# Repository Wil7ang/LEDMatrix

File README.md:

LEDMatrix
=========

LED Matrix display firmware.

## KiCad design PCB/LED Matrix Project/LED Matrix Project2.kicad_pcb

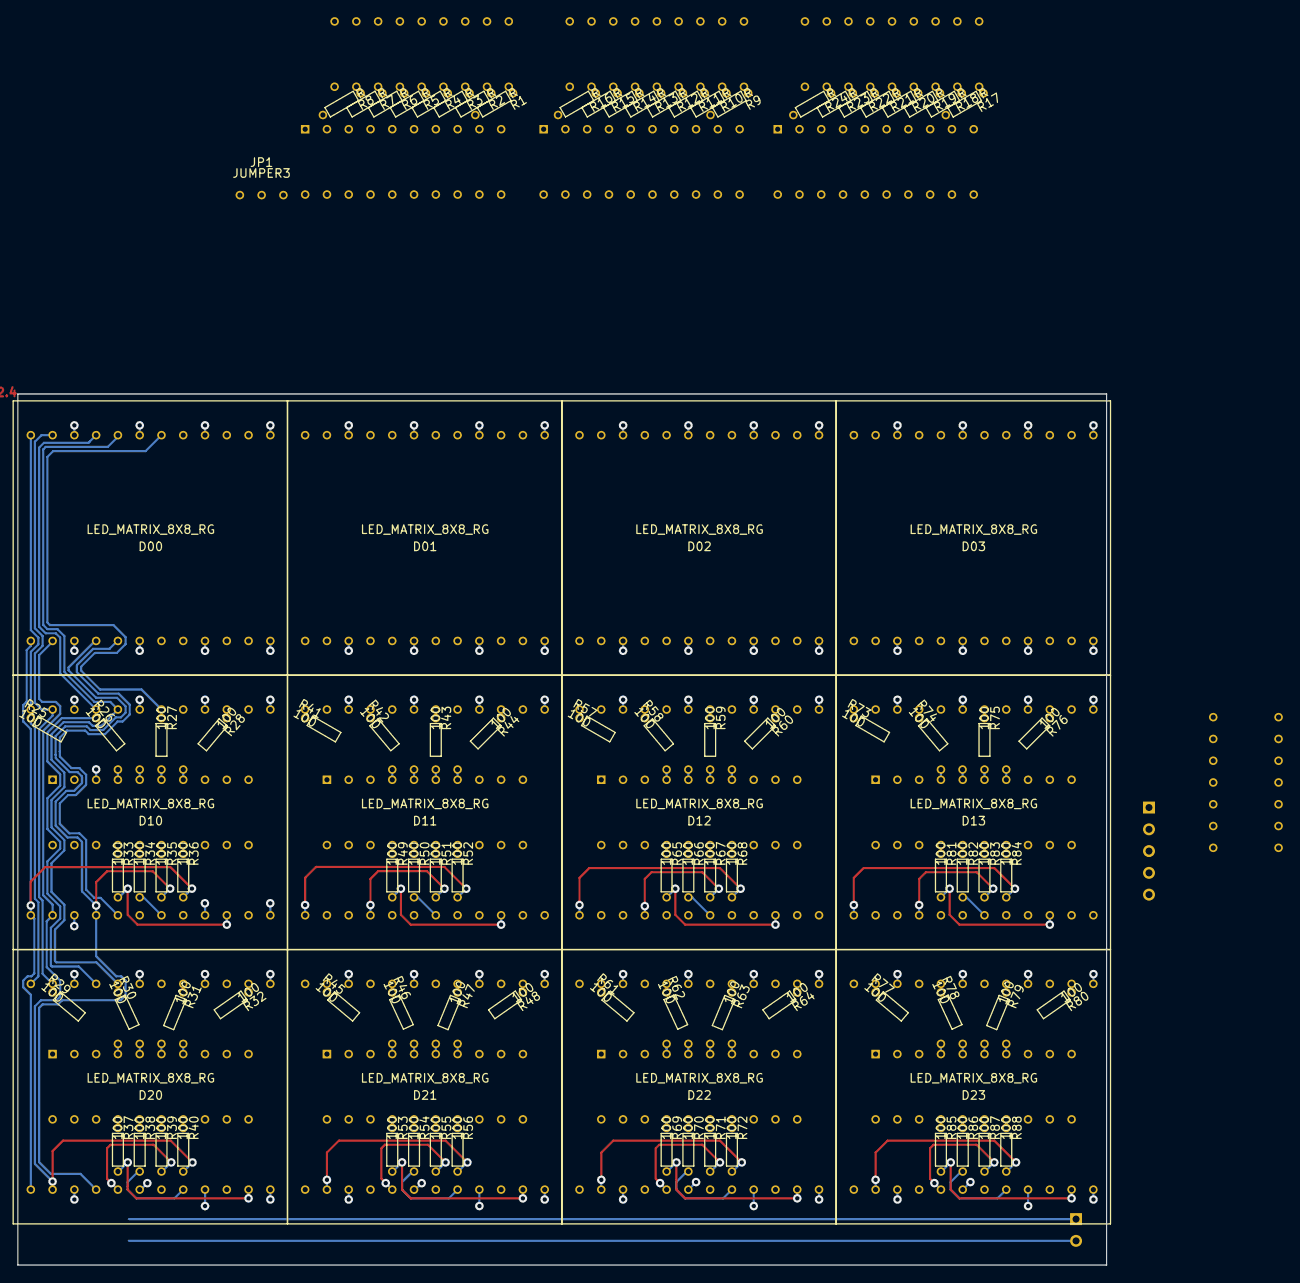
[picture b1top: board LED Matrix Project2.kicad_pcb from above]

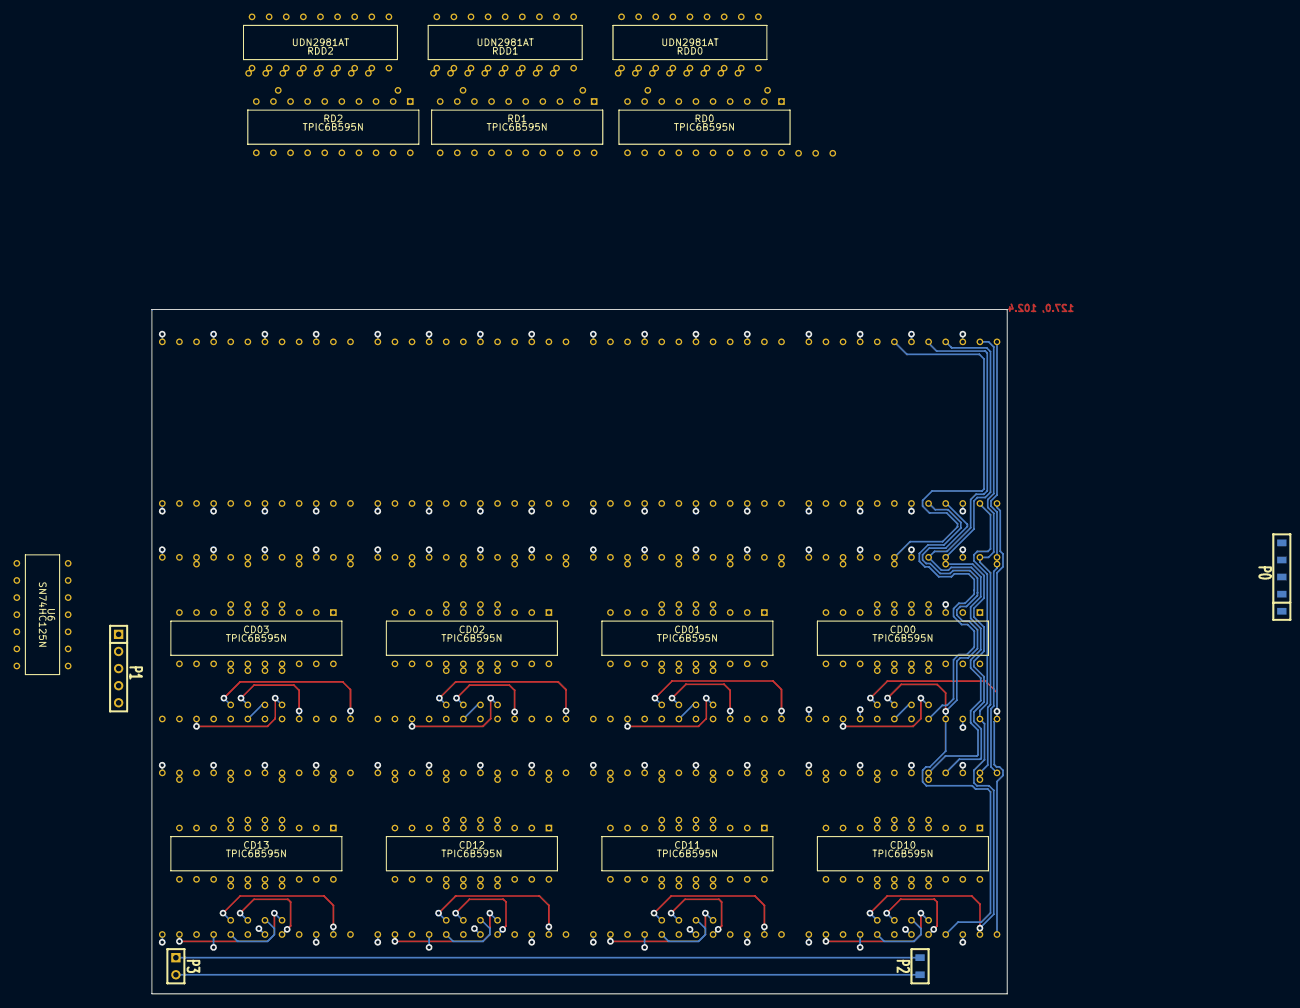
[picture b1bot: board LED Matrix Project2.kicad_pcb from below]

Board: 2 copper layers, 127.0 x 101.6 mm, 120 parts (19 on the bottom side), 199 nets.

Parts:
CD00, CD01, CD02, CD03, CD10, CD11, CD12, CD13: TPIC6B595N; TPIC6B595N-DIP
D00, D01, D02, D03, D10, D11, D12, D13, D20, D21, D22, D23: LED_MATRIX_8X8_RG; LEDMatrix8x8
JP1: JUMPER3; 3-Jumper
P0, P1: CONN_5; SIL-5
P2, P3: CONN_2; SIL-2
R1, R2, R3, R4, R5, R6, R7, R8, R9, R10, R11, R12, R13, R14, R15, R16, R17, R18, R19, R20, R21, R22, R23, R24: R; 1-8Resistor
R25, R26, R27, R28, R29, R30, R31, R32, R33, R34, R35, R36, R37, R38, R39, R40, R41, R42, R43, R44, R45, R46, R47, R48, R49, R50, R51, R52, R53, R54, R55, R56, R57, R58, R59, R60, R61, R62, R63, R64, R65, R66, R67, R68, R69, R70, R71, R72, R73, R74, R75, R76, R77, R78, R79, R80, R81, R82, R83, R84, R85, R86, R87, R88: 100; 1-8Resistor
RD0, RD1, RD2: TPIC6B595N; TPIC6B595N-DIP
RDD0, RDD1, RDD2: UDN2981AT
U6: SN74HC125N

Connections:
5Vcc: CD00.2, CD00.8, CD01.2, CD01.8, CD02.2, CD02.8, CD03.2, CD03.8, CD10.2, CD10.8, CD11.2, CD11.8, CD12.2, CD12.8, CD13.2, CD13.8, P2.2, P3.1, R1.2, R8.2, R9.2, R16.2, R17.2, R24.2, RD0.2, RD0.8, RD1.2, RD1.8, RD2.2, RD2.8, RDD0.9, RDD1.9, RDD2.9, U6.14
DATA IN: P0.3, RD0.3, U6.9
DATA IN 2: JP1.1, P0.1
DATA OUT: P1.5, U6.11
DATA OUT 1: P1.3, U6.8
DATA OUT RED: CD03.18, CD10.3
G: CD00.9, CD01.9, CD02.9, CD03.9, CD10.9, CD11.9, CD12.9, CD13.9, P0.2, P1.4, RD0.9, RD1.9, RD2.9
GND: CD00.10, CD00.11, CD00.19, CD01.10, CD01.11, CD01.19, CD02.10, CD02.11, CD02.19, CD03.10, CD03.11, CD03.19, CD10.10, CD10.11, CD10.19, CD11.10, CD11.11, CD11.19, CD12.10, CD12.11, CD12.19, CD13.10, CD13.11, CD13.19, P2.1, P3.2, RD0.10, RD0.11, RD0.19, RD1.10, RD1.11, RD1.19, RD2.10, RD2.11, RD2.19, RDD0.10, RDD1.10, RDD2.10, U6.1, U6.4, U6.7, U6.10, U6.13
unnamed: D03.4, D13.4, D23.4, R83.2
unnamed: D03.1, D13.1, D23.1, R84.2
unnamed: D03.7, D13.7, D23.7, R82.2
unnamed: D03.10, D13.10, D23.10, R81.2
unnamed: D10.3, D11.3, D12.3, D13.3, RDD1.15
unnamed: R23.1, RD2.6, RDD2.7
unnamed: R24.1, RD2.7, RDD2.8
unnamed: R22.1, RD2.5, RDD2.6
unnamed: R21.1, RD2.4, RDD2.5
unnamed: R17.1, RD2.17, RDD2.1
unnamed: R20.1, RD2.14, RDD2.4
unnamed: R19.1, RD2.15, RDD2.3
unnamed: R18.1, RD2.16, RDD2.2
unnamed: D00.21, D10.21, D20.21, R26.1
unnamed: D03.15, D13.15, D23.15, R76.1
unnamed: D03.18, D13.18, D23.18, R75.1
unnamed: D03.21, D13.21, D23.21, R74.1
unnamed: D03.24, D13.24, D23.24, R73.1
unnamed: D03.8, D13.8, D23.8, R86.2
unnamed: D03.2, D13.2, D23.2, R88.2
unnamed: D03.14, D13.14, D23.14, R80.1
unnamed: D03.17, D13.17, D23.17, R79.1
unnamed: D03.20, D13.20, D23.20, R78.1
unnamed: D03.23, D13.23, D23.23, R77.1
unnamed: D01.24, D11.24, D21.24, R41.1
unnamed: D10.12, D11.12, D12.12, D13.12, RDD1.18
unnamed: D10.9, D11.9, D12.9, D13.9, RDD1.17
unnamed: D10.6, D11.6, D12.6, D13.6, RDD1.16
unnamed: R13.1, RD1.4, RDD1.5
unnamed: R10.1, RD1.16, RDD1.2
unnamed: R9.1, RD1.17, RDD1.1
unnamed: R14.1, RD1.5, RDD1.6
unnamed: R11.1, RD1.15, RDD1.3
unnamed: R12.1, RD1.14, RDD1.4
unnamed: D10.13, D11.13, D12.13, D13.13, RDD1.11
unnamed: D10.16, D11.16, D12.16, D13.16, RDD1.12
unnamed: D10.19, D11.19, D12.19, D13.19, RDD1.13
unnamed: D10.22, D11.22, D12.22, D13.22, RDD1.14
unnamed: R16.1, RD1.7, RDD1.8
unnamed: R15.1, RD1.6, RDD1.7
unnamed: CD00.18, CD01.3
unnamed: CD01.18, CD02.3
unnamed: CD02.18, CD03.3
unnamed: CD10.18, CD11.3
unnamed: CD11.18, CD12.3
unnamed: CD12.18, CD13.3
unnamed: CD00.3, JP1.2
unnamed: JP1.3, RD2.18
unnamed: RD1.18, RD2.3
unnamed: RD0.18, RD1.3
unnamed: CD13.18, U6.12
unnamed: D20.19, D21.19, D22.19, D23.19, RDD2.13
unnamed: D20.13, D21.13, D22.13, D23.13, RDD2.11
unnamed: D20.3, D21.3, D22.3, D23.3, RDD2.15
unnamed: D20.9, D21.9, D22.9, D23.9, RDD2.17
unnamed: D20.22, D21.22, D22.22, D23.22, RDD2.14
unnamed: D20.16, D21.16, D22.16, D23.16, RDD2.12
unnamed: D20.12, D21.12, D22.12, D23.12, RDD2.18
unnamed: D20.6, D21.6, D22.6, D23.6, RDD2.16
unnamed: D02.21, D12.21, D22.21, R58.1
unnamed: D02.15, D12.15, D22.15, R60.1
unnamed: D02.20, D12.20, D22.20, R62.1
unnamed: D00.20, D10.20, D20.20, R30.1
unnamed: D00.15, D10.15, D20.15, R28.1
unnamed: D03.5, D13.5, D23.5, R87.2
unnamed: D03.11, D13.11, D23.11, R85.2
unnamed: CD12.17, R69.1
unnamed: D02.11, D12.11, D22.11, R69.2
unnamed: D02.14, D12.14, D22.14, R64.1
unnamed: CD12.7, R64.2
unnamed: D02.17, D12.17, D22.17, R63.1
unnamed: CD12.6, R63.2
unnamed: CD12.5, R62.2
unnamed: CD12.4, R61.2
unnamed: CD03.16, R82.1
unnamed: CD03.17, R81.1
unnamed: CD03.14, R84.1
unnamed: CD03.15, R83.1
unnamed: CD03.7, R76.2
unnamed: CD03.6, R75.2
unnamed: CD03.5, R74.2
unnamed: CD03.4, R73.2
unnamed: CD02.14, R68.1
unnamed: CD02.15, R67.1
unnamed: CD02.16, R66.1
unnamed: CD02.17, R65.1
unnamed: D02.1, D12.1, D22.1, R68.2
unnamed: D02.7, D12.7, D22.7, R66.2
unnamed: CD02.7, R60.2
unnamed: CD02.6, R59.2
unnamed: CD02.5, R58.2
unnamed: CD02.4, R57.2
unnamed: CD12.14, R72.1
unnamed: CD12.15, R71.1
unnamed: CD12.16, R70.1
unnamed: D02.2, D12.2, D22.2, R72.2
unnamed: D02.18, D12.18, D22.18, R59.1
unnamed: CD13.14, R88.1
unnamed: CD13.15, R87.1
unnamed: CD13.16, R86.1
unnamed: CD13.17, R85.1
unnamed: CD13.7, R80.2
unnamed: CD13.6, R79.2
unnamed: CD13.5, R78.2
unnamed: CD13.4, R77.2
unnamed: CD10.16, R38.1
unnamed: CD10.17, R37.1
unnamed: D00.11, D10.11, D20.11, R37.2
unnamed: D00.14, D10.14, D20.14, R32.1
unnamed: CD10.7, R32.2
unnamed: D00.17, D10.17, D20.17, R31.1
unnamed: CD10.6, R31.2
unnamed: CD10.5, R30.2
unnamed: CD10.4, R29.2
unnamed: R5.1, RD0.4, RDD0.5
unnamed: CD10.15, R39.1
unnamed: CD10.14, R40.1
unnamed: D00.2, D10.2, D20.2, R40.2
unnamed: R4.1, RD0.14, RDD0.4
unnamed: R6.1, RD0.5, RDD0.6
unnamed: R7.1, RD0.6, RDD0.7
unnamed: R8.1, RD0.7, RDD0.8
unnamed: R1.1, RD0.17, RDD0.1
unnamed: R2.1, RD0.16, RDD0.2
unnamed: D00.24, D10.24, D20.24, R25.1
unnamed: D00.23, D10.23, D20.23, R29.1
unnamed: CD00.4, R25.2
unnamed: CD00.5, R26.2
unnamed: CD00.6, R27.2
unnamed: CD00.7, R28.2
unnamed: D00.10, D10.10, D20.10, R33.2
unnamed: D00.8, D10.8, D20.8, R38.2
unnamed: D00.5, D10.5, D20.5, R39.2
unnamed: D00.4, D10.4, D20.4, R35.2
unnamed: CD00.17, R33.1
unnamed: D00.18, D10.18, D20.18, R27.1
unnamed: D00.7, D10.7, D20.7, R34.2
unnamed: CD00.16, R34.1
unnamed: CD00.15, R35.1
unnamed: D00.1, D10.1, D20.1, R36.2
unnamed: CD00.14, R36.1
unnamed: CD11.14, R56.1
unnamed: CD11.7, R48.2
unnamed: CD11.6, R47.2
unnamed: CD11.15, R55.1
unnamed: CD11.16, R54.1
unnamed: CD11.17, R53.1
unnamed: D01.2, D11.2, D21.2, R56.2
unnamed: CD11.5, R46.2
unnamed: CD11.4, R45.2
unnamed: CD01.4, R41.2
unnamed: CD01.5, R42.2
unnamed: D01.21, D11.21, D21.21, R42.1
unnamed: CD01.6, R43.2
unnamed: D01.18, D11.18, D21.18, R43.1
unnamed: CD01.7, R44.2
unnamed: D01.15, D11.15, D21.15, R44.1
unnamed: CD01.17, R49.1
unnamed: D02.4, D12.4, D22.4, R67.2
unnamed: D02.5, D12.5, D22.5, R71.2
unnamed: D02.8, D12.8, D22.8, R70.2
unnamed: D02.10, D12.10, D22.10, R65.2
unnamed: D02.23, D12.23, D22.23, R61.1
unnamed: D02.24, D12.24, D22.24, R57.1
unnamed: D01.7, D11.7, D21.7, R50.2
unnamed: D01.20, D11.20, D21.20, R46.1
unnamed: D01.17, D11.17, D21.17, R47.1
unnamed: D01.14, D11.14, D21.14, R48.1
unnamed: D01.11, D11.11, D21.11, R53.2
unnamed: D01.8, D11.8, D21.8, R54.2
unnamed: D01.4, D11.4, D21.4, R51.2
unnamed: D01.5, D11.5, D21.5, R55.2
unnamed: D01.10, D11.10, D21.10, R49.2
unnamed: D00.12, D01.12, D02.12, D03.12, RDD0.18
unnamed: D01.23, D11.23, D21.23, R45.1
unnamed: CD01.14, R52.1
unnamed: CD01.15, R51.1
unnamed: CD01.16, R50.1
unnamed: D01.1, D11.1, D21.1, R52.2
unnamed: D00.9, D01.9, D02.9, D03.9, RDD0.17
unnamed: D00.3, D01.3, D02.3, D03.3, RDD0.15
unnamed: D00.6, D01.6, D02.6, D03.6, RDD0.16
unnamed: R3.1, RD0.15, RDD0.3
unnamed: D00.19, D01.19, D02.19, D03.19, RDD0.13
unnamed: D00.22, D01.22, D02.22, D03.22, RDD0.14
unnamed: D00.16, D01.16, D02.16, D03.16, RDD0.12
unnamed: D00.13, D01.13, D02.13, D03.13, RDD0.11
RCK: CD00.12, CD01.12, CD02.12, CD03.12, CD10.12, CD11.12, CD12.12, CD13.12, P0.4, RD0.12, RD1.12, RD2.12, U6.5
RCK OUT: P1.2, U6.6
SRCK: CD00.13, CD01.13, CD02.13, CD03.13, CD10.13, CD11.13, CD12.13, CD13.13, P0.5, RD0.13, RD1.13, RD2.13, U6.2
SRCK OUT: P1.1, U6.3

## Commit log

2014-02-26 Initial code commit
2014-02-26 Add build script
2014-02-26 Fix std typo
2014-02-26 Fix missed semicolon
2014-02-26 Add font argument
2014-02-26 Error const char* should be cool
2014-02-26 Switch to targa font
2014-02-26 Unreverse characters
2014-02-26 Exclude tiny font from big font
2014-02-26 Reduce to 16
2014-02-26 Add initial support for tiny text
2014-02-26 Change position to reference correct tinyposition
2014-02-26 Add clock
2014-02-26 Hard fix for tiny ‘4’
2014-02-26 Catch run away no internet connection condition
2014-02-26 Changed time check location
2014-02-26 pthread fix
2014-02-26 Reorder definitions
2014-02-26 Fix string erase index
2014-02-26 Change time color to green
2014-02-26 Add support for negative offset
2014-02-26 Delay pthread
2014-02-26 Correct thread
2014-02-26 Add second argument to pthread_join
2014-02-27 Attempt fix at no internet crash
2014-02-27 Fix reload
2014-02-27 Add negative start offset
2014-02-27 Temporary disable offset increment
2014-02-27 Changed negative offset
2014-02-27 Add more print
2014-02-27 Test
2014-02-27 Fix start position
2014-02-27 Offset clock
2014-02-27 Increase text speed
2014-02-27 Add join thread
2014-02-28 Added CNN news source
2014-02-28 Fix color change
2014-02-28 Add PCB files
2014-03-02 Free mrss data
2014-03-02 Add engadget feed
2014-03-02 Fix typo
2014-03-02 Increase speed to 6
2014-03-09 Increase size to final 30
2014-03-09 Increase hwdebug time
2014-03-09 Disable hwdebug
2014-03-10 Change SPI speed
2014-03-10 Move clock position
2014-03-31 More optimizations
2014-03-31 Optimizations
2014-03-31 Slow speed
2014-03-31 Clean up code
2014-03-31 Add FPS counter
2014-03-31 FPS counter fix
2014-03-31 Fix FPS bug
2014-03-31 FPS fix
2014-04-02 Isolate frame rendering
2014-04-02 Revert..
2014-04-03 Reisolate frame rendering add news source identifier
2014-04-03 Syntax error
2014-04-03 Fix news source name change delay
2014-04-03 Missing semicolon
2014-04-03 Bug fixes
2014-04-03 Move names
2014-04-03 Bug fix
2014-04-03 Fix bug on charager ‘6’ Fix coloration order
2014-04-03 Color fixes
2014-04-06 Shrink space size in targafont
2014-04-06 Increase spacing to 8
2014-04-16 Test weather icons
2014-04-16 Fix width of ‘6’
2014-04-16 Missing commas
2014-04-16 Typo
2014-04-16 Fix incorrect array length
2014-04-16 Move test patterns
2014-04-16 Matrix reference error
2014-04-16 Add last two weather icon tests
2014-04-16 Reverse order of print
2014-04-16 Fix ‘Q’ print
2014-04-16 Add fix to larger letters
2014-04-16 Type collision
2014-05-14 Added weather report
2014-05-14 Add complete headers
2014-05-14 Change build order
2014-05-14 Local reference
2014-05-14 WTF?
2014-05-14 Fix high temperature
2014-05-14 Change temperature high to integer
2014-05-14 Weather timer never resets.
2015-09-13 Fix frame delay
2017-02-12 Change weather location to RWC
2017-02-12 Add openweather appid argument
2017-02-12 Update openweather API
2017-02-12 Fix macro typo
2017-02-12 Add temperature unit to temperature data
2017-02-12 Remove weather icons
2018-03-04 Make font selection generic Update deprecated RSS URL's Disable upper case transform
2018-03-04 const needed
2018-03-04 Make more generic
2018-03-04 Remove excess pixel in letter 'g'
2018-03-05 Fix pointers
2018-03-05 Change to generic fontArrayWidth
2018-03-05 Increase scroll speed
2018-03-05 Remove extraneous pixel in letter j
2018-03-05 Change scroll speed to 1.25
2018-03-05 Add const for sansfont width
2018-03-05 Redo color conditions
2018-03-05 Refactor colors
2018-03-05 Refactor threading
